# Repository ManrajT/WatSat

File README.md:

WatSat
======

Code for the Waterloo Satellite Team (ie. Arduino)

TODO:
- in comp/comm.py activate -> change the post sensor data to a value that makes sense
- TESTING!

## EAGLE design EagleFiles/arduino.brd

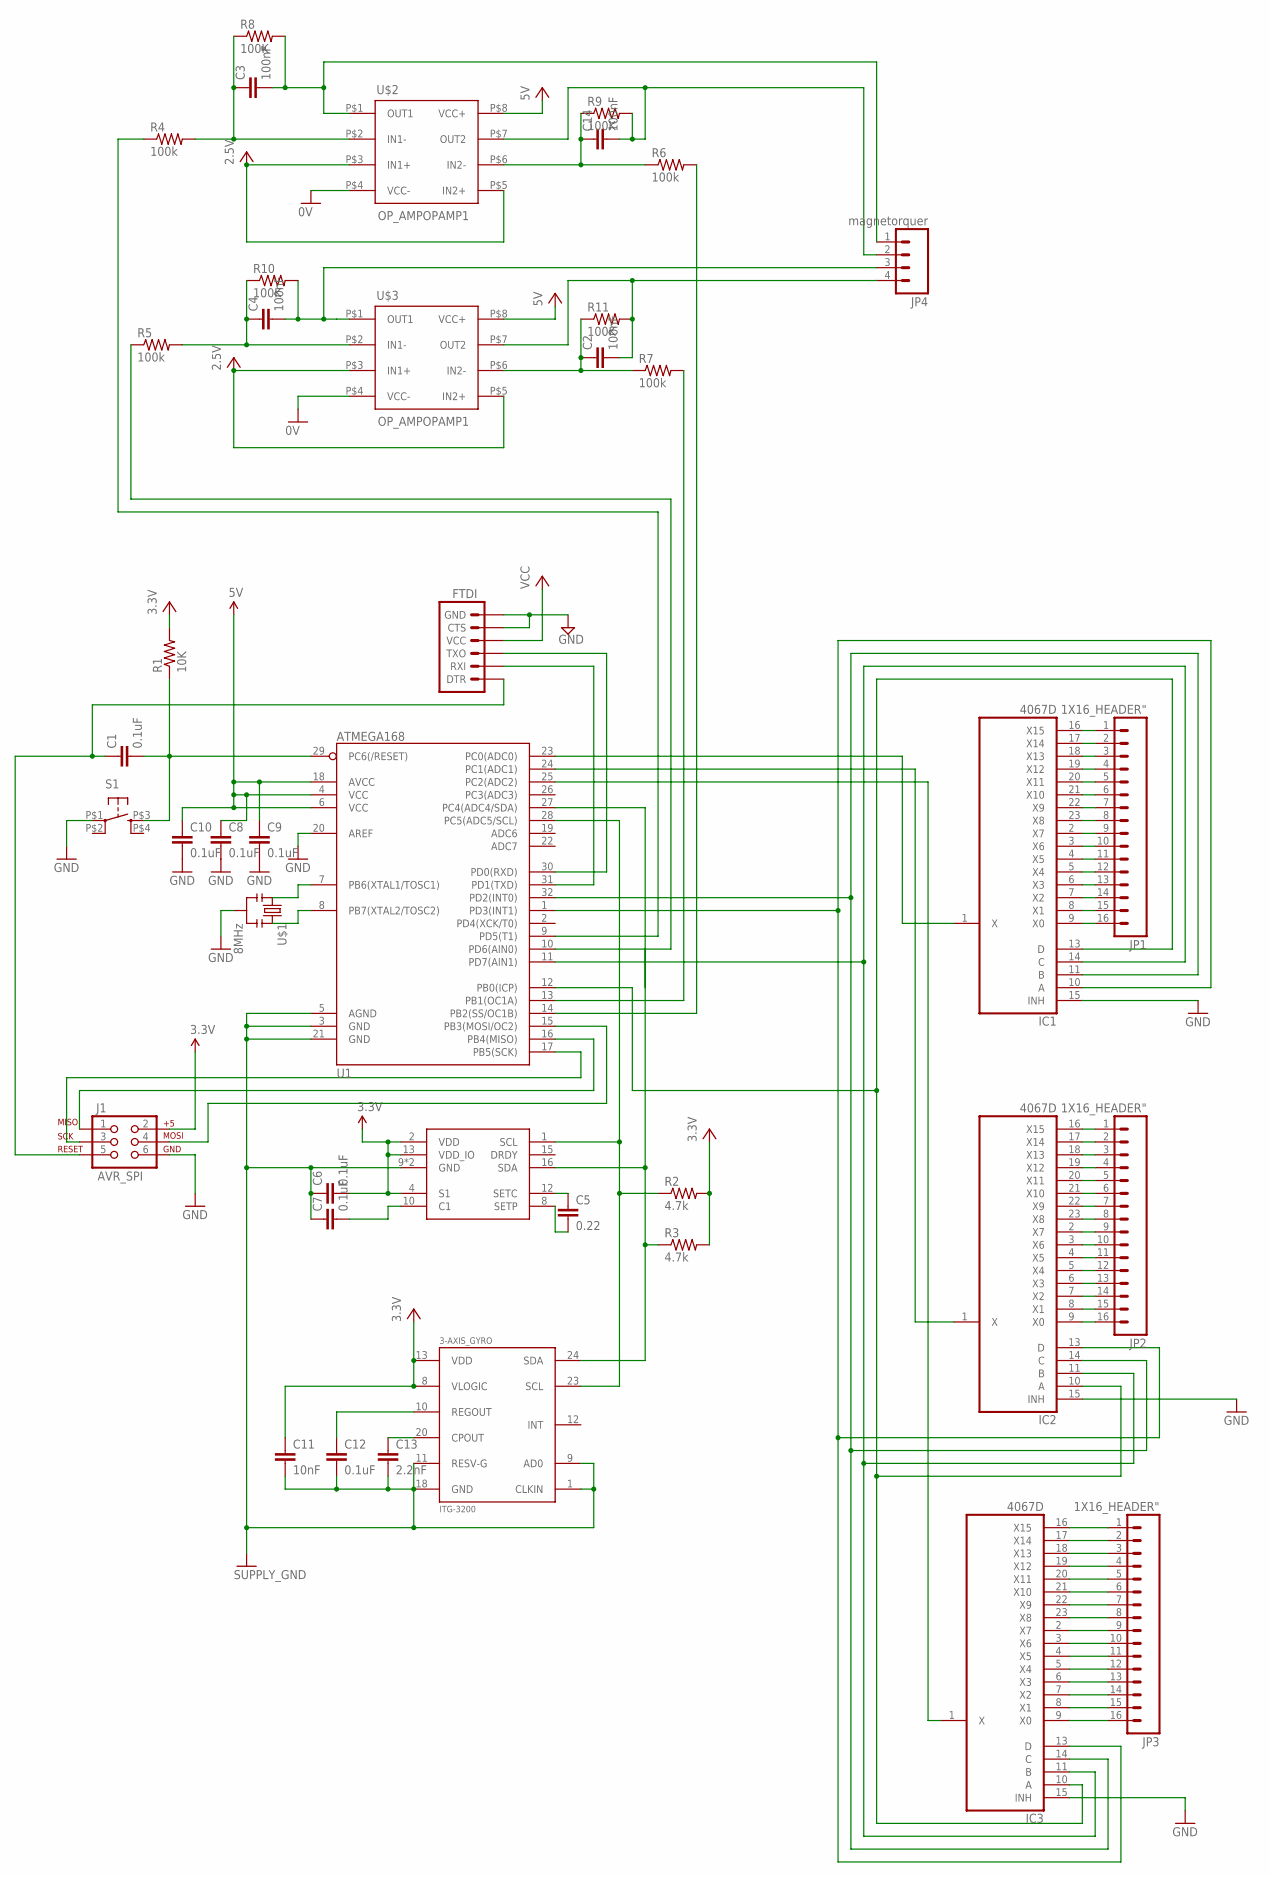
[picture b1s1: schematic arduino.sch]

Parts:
3-AXIS_GYRO: ITG-3200; QFN-24
3-AXIS_MAG: HMC5883L; LPCC16
C1, C8, C9, C10: 0.1uF; 0603-CAP
C2, C3, C4, C14: 100nF; 0402-CAP
C5: 0.22; 0402-CAP
C6, C7, C12: 0.1uF; 0402-CAP
C11: 10nF; 0402-CAP
C13: 2.2nF; 0402-CAP
FTDI: ARDUINO_SERIAL_PROGRAMPTH; 1X06
IC1, IC2, IC3: 4067D; SO24W
J1: AVR_SPI; 2X3
JP1, JP2, JP3: 1X16_HEADER"; 1X16_HEADER
JP4: magnetorquer; 1X04_HEADER
R1: 10K; 0805
R2, R3: 4.7k; 0805
R4, R5, R6, R7: 100k; 0805
R8, R9, R10, R11: 100K; 0805
S1: TAC_SWITCHKSA_SEALED; KSA_SEALED_TAC_SWITCH
U1: ATMEGA168; TQFP32-08
U$1: 8MHz; RESONATOR
U$2, U$3: OP_AMPOPAMP1; OPAMP

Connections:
GND: 3-AXIS_GYRO.1 (CLKIN), 3-AXIS_GYRO.9 (AD0), 3-AXIS_GYRO.11 (RESV-G), 3-AXIS_GYRO.18 (GND), 3-AXIS_MAG.9 (GND), 3-AXIS_MAG.11 (GND), C6.1, C7.1, C8.2, C9.2, C10.2, C11.2, C12.2, C13.2, FTDI.5 (CTS), FTDI.6 (GND), IC1.15 (INH), IC2.15 (INH), IC3.15 (INH), J1.6, S1.P$1 (1), U1.3 (GND), U1.5 (AGND), U1.20 (AREF), U1.21 (GND), U$1.2, U$2.P$4 (VCC-), U$3.P$4 (VCC-)
unnamed: IC1.16 (X15), JP1.1
unnamed: IC1.14 (C), IC2.11 (B), IC3.11 (B), U1.11 (PD7(AIN1))
unnamed: IC1.11 (B), IC2.14 (C), IC3.14 (C), U1.32 (PD2(INT0))
unnamed: IC1.10 (A), IC2.13 (D), IC3.13 (D), U1.1 (PD3(INT1))
unnamed: IC1.1 (X), U1.23 (PC0(ADC0))
unnamed: IC2.1 (X), U1.24 (PC1(ADC1))
unnamed: IC1.13 (D), IC2.10 (A), IC3.10 (A), U1.12 (PB0(ICP))
unnamed: IC1.17 (X14), JP1.2
unnamed: IC1.18 (X13), JP1.3
unnamed: IC1.19 (X12), JP1.4
unnamed: IC1.20 (X11), JP1.5
unnamed: IC1.21 (X10), JP1.6
unnamed: IC1.22 (X9), JP1.7
unnamed: IC1.23 (X8), JP1.8
unnamed: IC1.2 (X7), JP1.9
unnamed: IC1.3 (X6), JP1.10
unnamed: IC1.4 (X5), JP1.11
unnamed: IC1.5 (X4), JP1.12
unnamed: IC1.6 (X3), JP1.13
unnamed: IC1.7 (X2), JP1.14
unnamed: IC1.8 (X1), JP1.15
unnamed: IC1.9 (X0), JP1.16
unnamed: IC2.16 (X15), JP2.1
unnamed: IC2.17 (X14), JP2.2
unnamed: IC2.18 (X13), JP2.3
unnamed: IC2.19 (X12), JP2.4
unnamed: IC2.20 (X11), JP2.5
unnamed: IC2.21 (X10), JP2.6
unnamed: IC2.22 (X9), JP2.7
unnamed: IC2.23 (X8), JP2.8
unnamed: IC2.2 (X7), JP2.9
unnamed: IC2.3 (X6), JP2.10
unnamed: IC2.4 (X5), JP2.11
unnamed: IC2.5 (X4), JP2.12
unnamed: IC2.6 (X3), JP2.13
unnamed: IC2.7 (X2), JP2.14
unnamed: IC2.8 (X1), JP2.15
unnamed: IC2.9 (X0), JP2.16
unnamed: C1.1, FTDI.1 (DTR), J1.5
unnamed: C1.2, R1.1, S1.P$3 (3), U1.29 (PC6(/RESET))
unnamed: 3-AXIS_GYRO.23 (SCL), 3-AXIS_MAG.1 (SCL), R2.1, U1.28 (PC5(ADC5/SCL))
unnamed: IC3.1 (X), U1.25 (PC2(ADC2))
unnamed: 3-AXIS_GYRO.24 (SDA), 3-AXIS_MAG.16 (SDA), R3.1, U1.27 (PC4(ADC4/SDA))
unnamed: 3-AXIS_MAG.12 (SETC), C5.1
unnamed: 3-AXIS_MAG.8 (SETP), C5.2
unnamed: IC3.16 (X15), JP3.1
unnamed: IC3.17 (X14), JP3.2
unnamed: IC3.18 (X13), JP3.3
unnamed: IC3.19 (X12), JP3.4
unnamed: IC3.20 (X11), JP3.5
unnamed: IC3.21 (X10), JP3.6
unnamed: IC3.22 (X9), JP3.7
unnamed: IC3.23 (X8), JP3.8
unnamed: IC3.2 (X7), JP3.9
unnamed: IC3.3 (X6), JP3.10
unnamed: IC3.4 (X5), JP3.11
unnamed: IC3.5 (X4), JP3.12
unnamed: IC3.6 (X3), JP3.13
unnamed: IC3.7 (X2), JP3.14
unnamed: IC3.8 (X1), JP3.15
unnamed: IC3.9 (X0), JP3.16
unnamed: 3-AXIS_MAG.10 (C1), C7.2
unnamed: R5.1, U1.10 (PD6(AIN0))
unnamed: 3-AXIS_GYRO.20 (CPOUT), C13.1
unnamed: 3-AXIS_GYRO.10 (REGOUT), C12.1
unnamed: C3.2, JP4.1, R8.2, U$2.P$1 (OUT1)
unnamed: J1.1, U1.16 (PB4(MISO))
unnamed: J1.3, U1.17 (PB5(SCK))
unnamed: U1.7 (PB6(XTAL1/TOSC1)), U$1.1
unnamed: U1.8 (PB7(XTAL2/TOSC2)), U$1.3
unnamed: J1.4, U1.15 (PB3(MOSI/OC2))
unnamed: R7.2, U1.13 (PB1(OC1A))
unnamed: R4.1, U1.9 (PD5(T1))
unnamed: R6.2, U1.14 (PB2(SS/OC1B))
unnamed: C4.1, R5.2, R10.1, U$3.P$2 (IN1-)
unnamed: C14.1, R6.1, R9.1, U$2.P$6 (IN2-)
unnamed: C2.1, R7.1, R11.1, U$3.P$6 (IN2-)
unnamed: C4.2, JP4.3, R10.2, U$3.P$1 (OUT1)
unnamed: FTDI.3 (TXO), U1.30 (PD0(RXD))
unnamed: FTDI.2 (RXI), U1.31 (PD1(TXD))
unnamed: C2.2, JP4.4, R11.2, U$3.P$7 (OUT2)
unnamed: C3.1, R4.2, R8.1, U$2.P$2 (IN1-)
unnamed: C14.2, JP4.2, R9.2, U$2.P$7 (OUT2)
VCC: 3-AXIS_GYRO.8 (VLOGIC), 3-AXIS_GYRO.13 (VDD), 3-AXIS_MAG.2 (VDD), 3-AXIS_MAG.4 (S1), 3-AXIS_MAG.13 (VDD_IO), C6.2, C8.1, C9.1, C10.1, C11.1, FTDI.4 (VCC), J1.2, R1.2, R2.2, R3.2, U1.4 (VCC), U1.6 (VCC), U1.18 (AVCC), U$2.P$3 (IN1+), U$2.P$5 (IN2+), U$2.P$8 (VCC+), U$3.P$3 (IN1+), U$3.P$5 (IN2+), U$3.P$8 (VCC+)
VDD: IC1.24 (VDD), IC2.24 (VDD), IC3.24 (VDD)
VSS: IC1.12 (VSS), IC2.12 (VSS), IC3.12 (VSS)

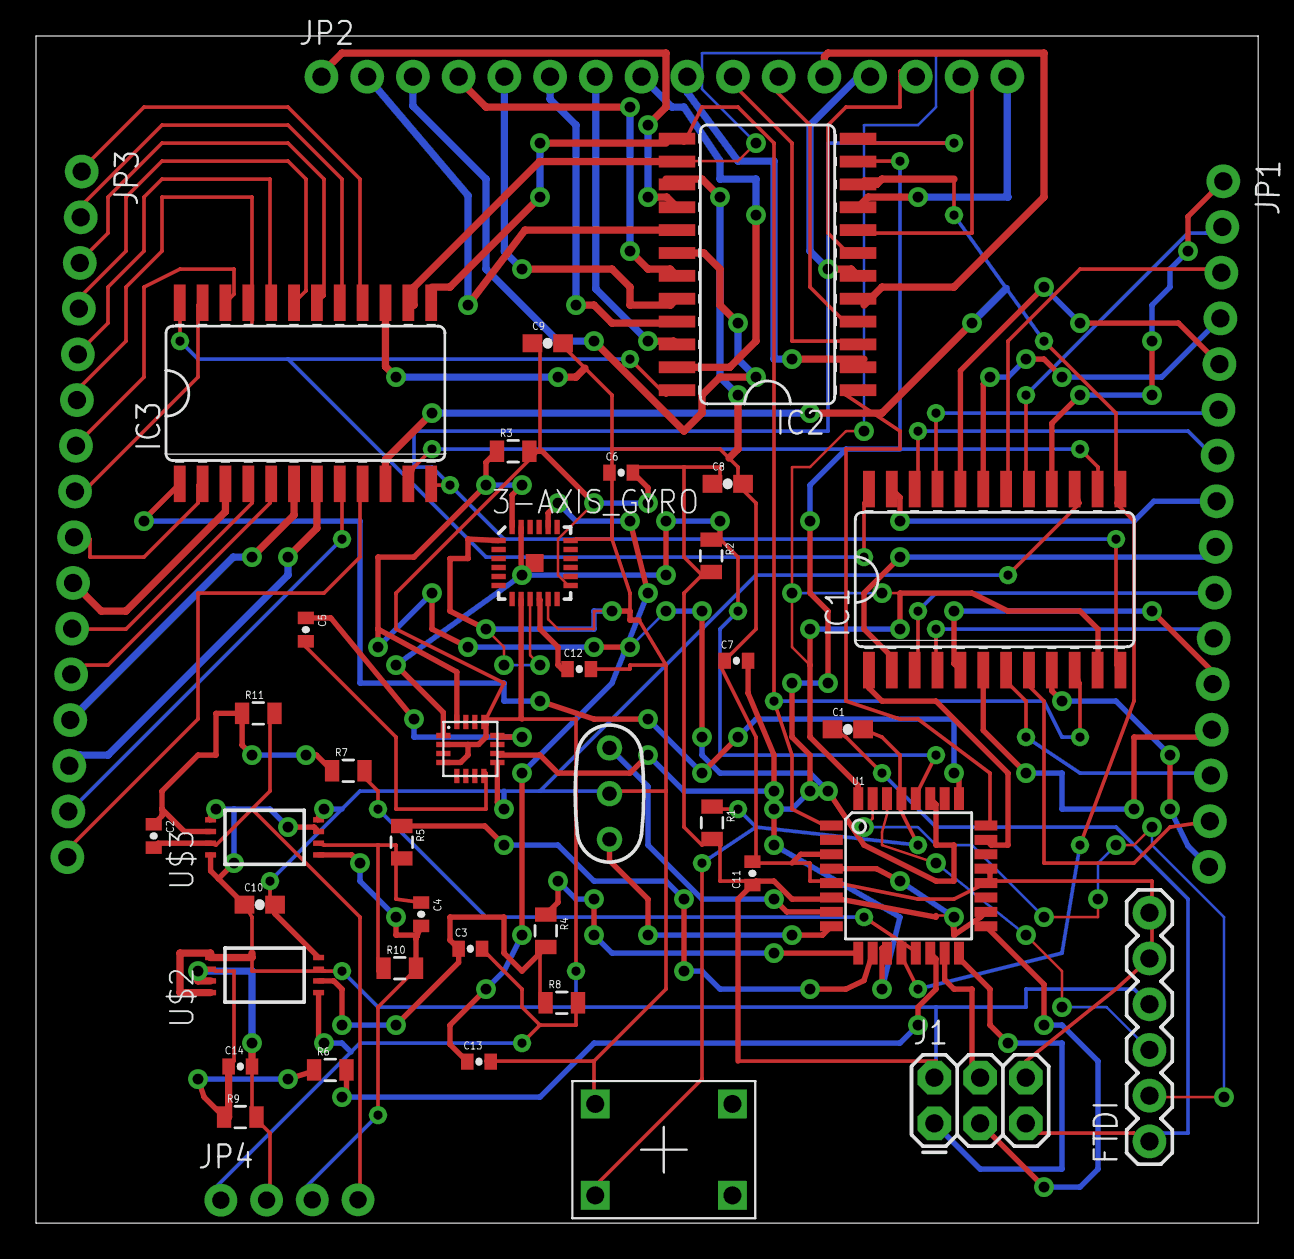
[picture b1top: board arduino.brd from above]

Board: 2 copper layers, 67.9 x 66.0 mm, 41 parts (0 on the bottom side), 87 nets.

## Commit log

2014-04-02 Very rough arduino pseudocode for reading sensor data
2014-04-05 added file for proposed architecture
    includes proposed file structure and links to
    resources (how to write a library and communicating
    with computing)
2014-04-06 prototype of script to communicate with arduino
    assumes:
    - python 2.7, pyserial are available
    - the arduino is attached to the computer
2014-04-06 added _prep_request function to python code
    goal of this function is to clarify when requests
    will be made to the arduino. This means the arduino
    will wait for the python script to ask for data and then
    read sensor data.
2014-04-06 corresponding changes to the arduino code
    follows the suit of the python script. In the
    main loop it waits until a 'get' or 'post' is
    needed and then the arduino will respond accordingly
    (response not implemented)
2014-04-08 before pull
2014-04-09 Wrote and Tested selectLine function (for selecting control line)
2014-05-08 serial working
2014-05-08 put arduino code in it's own dir
2014-05-13 changes to tests and arduino code
    - added test folder
    - changed debugging for arduino
    - moved test.py to comp/comm.py
2014-05-13 updated communication b/w arduino and comp
    - added delay to arduino code to make readline
    in python work
    - added __init__ to comp so can use it
    - made comm.py have a class
    - added .gitignore
2014-05-13 updated the activate fucntion to run workflow
2014-05-14 finished first unittests
    - added open/close methods to comp/comm.py
    - added test for getting sensor data, activate
    - still outstanding is post changes because not
    yet implemented in code
2014-05-14 removed TODO
    - no need for docopt: will make things
    more difficult than they need to be
2014-05-17 started putting together class for sensors
    will make accessing data much easier
2014-05-18 made header file for SBoard
    will support functions to:
    - read in data
    - write data to serial port
2014-05-18 finished adding private methods
2014-05-19 added struct for sensors
    will make reading data clean and easy
    ... sweeet
2014-05-19 added stuff to be able to control pins
    NOTE: not implemented yet
2014-05-20 finished: should have full functionallity
    outstanding: testing
2014-05-20 everything compiles (yay)
2014-05-20 started on generator function
    purpose is to turn string from we
    get from the arduino into a dict
    so that data can be easily accessed
    in controlled algorithms
2014-05-21 added generator function + unit test
    - added print to test sensor get
    - added __init__
2014-05-21 removed outdated zip file
2014-05-22 updated arduino code to implement all the changes
    also did:
    - update unittest to cover getting a lot of data
    - fixed post_changes to make sense
    todo:
    - write arduino function to do stuff on post request
2014-05-22 added method to write changes to torquers
2014-05-22 added some todo's
2014-05-23 removed unused libaries
2014-05-25 finished hacking together fixes for the lib
2014-05-25 defined structure for adding imu
    - also added test
2014-05-26 Added HMC5883L lib and imu stuff
    :)
2014-05-26 updated test for env test
2014-05-26 fixed unittest for env testing
2014-05-26 derp
2014-05-26 more derp
2014-06-18 added eagle files or arduino
    basically just power and muxs
2014-06-19 added another mux
2014-06-19 added most of the ic's
    TODO:
    - power
    - hook up mux's right
    - verification
    - board
2014-06-22 fixed the i2c stuff
2014-06-22 removed mux connection to rx and tx
2014-06-22 added serial interface
    - will need use to ftdi cable to use
    - do we want to put the ftdi on the
    board so all that is needed is a usb
2014-06-22 changed ATMEG chip + made the power more right
    - the previous atmega used dip (no good)
    - new chip us surface mount
    - modelled power stuff on the sparkfun razor
    9 degree of freedom imu
2014-06-22 added connections for muxs
    hopefully in the right spot this time...
2014-06-22 finished first rev
2014-06-24 made changes suggested by Edrick
    - switched ftdi rx/tx times
    - added caps to each power line in to ATMEGA
    - fixed SDA connection for 12c bus
    - fixed gyro connections
2014-06-26 made the fixes
2014-06-29 added the lpf because forgot that before
2014-07-02 made some changes?
2014-07-17 adcs board
2014-07-24 finally did board layout
    now to fix all the errors :(
2014-07-31 added interrupt code for RX complete
    - is an attempt to make information transfer
    a bit more reliable.
    - not yet tested on arduino but should be good,
    to test just run integration tests
2014-08-07 I think I got everything on com side
    - added decorators to open/close arduino port
    - removed all imu stuff
    - other minor things....
2014-08-07 updated tests to match new ADCSArduino class
    - since it no longer uses imu
2014-08-07 fixed misspelled variables
2014-08-21 fixed the bugs in decorators
    - minor modification to arduino code
    - should be working correctly
    - tested with arduino
    - failed test for retrieving data as expected
2015-01-29 can get info from arduino
    - removed the decorator from the function
    that gets the info

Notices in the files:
parts and their libraries:
SparkFun: Licensing: CC v3.0 Share-Alike You are welcome to use this library for commercial purposes.
